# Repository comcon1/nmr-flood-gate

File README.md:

# Flood-gate for naked mole rats

The project describes the flood-gate for installation into the colony of naked mole rats or other small animals.

Flood-gate includes two doors with solenoid locks. There are four lines of IR beam interrupt detectors: one before every door and one after every door. 
Before the door, we have two beams perpendicular to each other and commutated with 'OR' logic. After the door, we have a single ray from up to bottom.

Beams are designed as four boards connected with wires located around the central tube: two beam receiver boards and, correspondingly, two beam transmitter boards.

# Project structure

Into the `flood-gate-3d`, we put 3D drafts of the general structure of the flood-gate.

2D drafts suitable for laser cut or CNC milling are located in `flood-gate-2d`.

The KICAD project for receiver and transmitter boards is in `emitter-reciever`.

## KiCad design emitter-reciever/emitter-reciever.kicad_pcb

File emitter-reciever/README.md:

# Emitter and Reciever boards

Project contains 4 boards:
* Emitter-1
* Emitter-2
* Reciever-1
* Reciever-2

Reciever boards connects each other with 4 wires. Emitters connects any reciever or each other with 2 wires (G, +5V).
Reciever-2 board has external interface which can be connected to the controller.

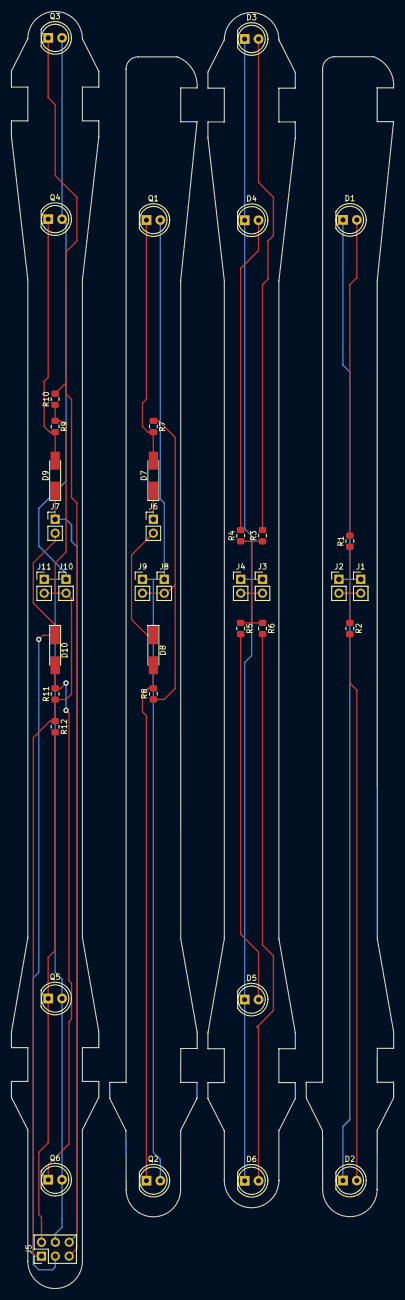
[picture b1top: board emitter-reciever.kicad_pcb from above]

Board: 2 copper layers, 70.0 x 234.0 mm, 39 parts (0 on the bottom side), 24 nets.

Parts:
D1, D2, D3, D4, D5, D6: LED; LED_D5.0mm
D7, D8, D9, D10: D; D_MiniMELF_Handsoldering
J1, J2, J3, J4, J6, J7, J8, J9, J10, J11: Conn_01x02; PinHeader_1x02_P2.54mm_Vertical
J5: Conn_02x03_Odd_Even; PinHeader_2x03_P2.54mm_Vertical
Q1, Q2, Q3, Q4, Q5, Q6: Q_Photo_NPN; LED_D5.0mm
R1, R2, R3, R4, R5, R6, R7, R8, R9, R10, R11, R12: R; R_0805_2012Metric_Pad1.15x1.40mm_HandSolder

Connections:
unnamed: D1.1, D2.1, J1.1, J2.1
unnamed: D1.2, R1.2
unnamed: D2.2, R2.2
unnamed: D3.1, D4.1, D5.1, D6.1, J3.1, J4.1
unnamed: D3.2, R3.2
unnamed: D4.2, R4.2
unnamed: D5.2, R5.2
unnamed: D6.2, R6.2
unnamed: D7.1, J6.1
unnamed: D7.2, Q1.1, R7.2
unnamed: D8.1, J6.2
unnamed: D8.2, Q2.1, R8.2
unnamed: D9.1, J5.6, J7.1
unnamed: D9.2, Q4.1, R9.2
unnamed: D10.1, J5.3, J7.2
unnamed: D10.2, Q6.1, R11.2
unnamed: J1.2, J2.2, R1.1, R2.1
unnamed: J3.2, J4.2, R3.1, R4.1, R5.1, R6.1
unnamed: J5.2, Q5.1, R12.2
unnamed: J5.5, Q3.1, R10.2
unnamed: J8.1, J9.1, Q1.2, Q2.2
unnamed: J8.2, J9.2, R7.1, R8.1
unnamed: J5.4, J10.1, J11.1, Q3.2, Q4.2, Q5.2, Q6.2
unnamed: J5.1, J10.2, J11.2, R9.1, R10.1, R11.1, R12.1

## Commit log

2019-12-03 put initial version of everything
2019-12-03 fix README
2019-12-03 fix image in README
2019-12-03 emitter-reciever kicad project added
2019-12-04 add manual on boards
